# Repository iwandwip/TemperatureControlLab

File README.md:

# Temperature Control Lab - AP Monitor
The temperature control lab is an application of feedback control with an Arduino, an LED, two heaters, and two temperature sensors. The heater power output is adjusted to maintain a desired temperature setpoint. Thermal energy from the heater is transferred by conduction, convection, and radiation to the temperature sensor. Heat is also transferred away from the device to the surroundings.

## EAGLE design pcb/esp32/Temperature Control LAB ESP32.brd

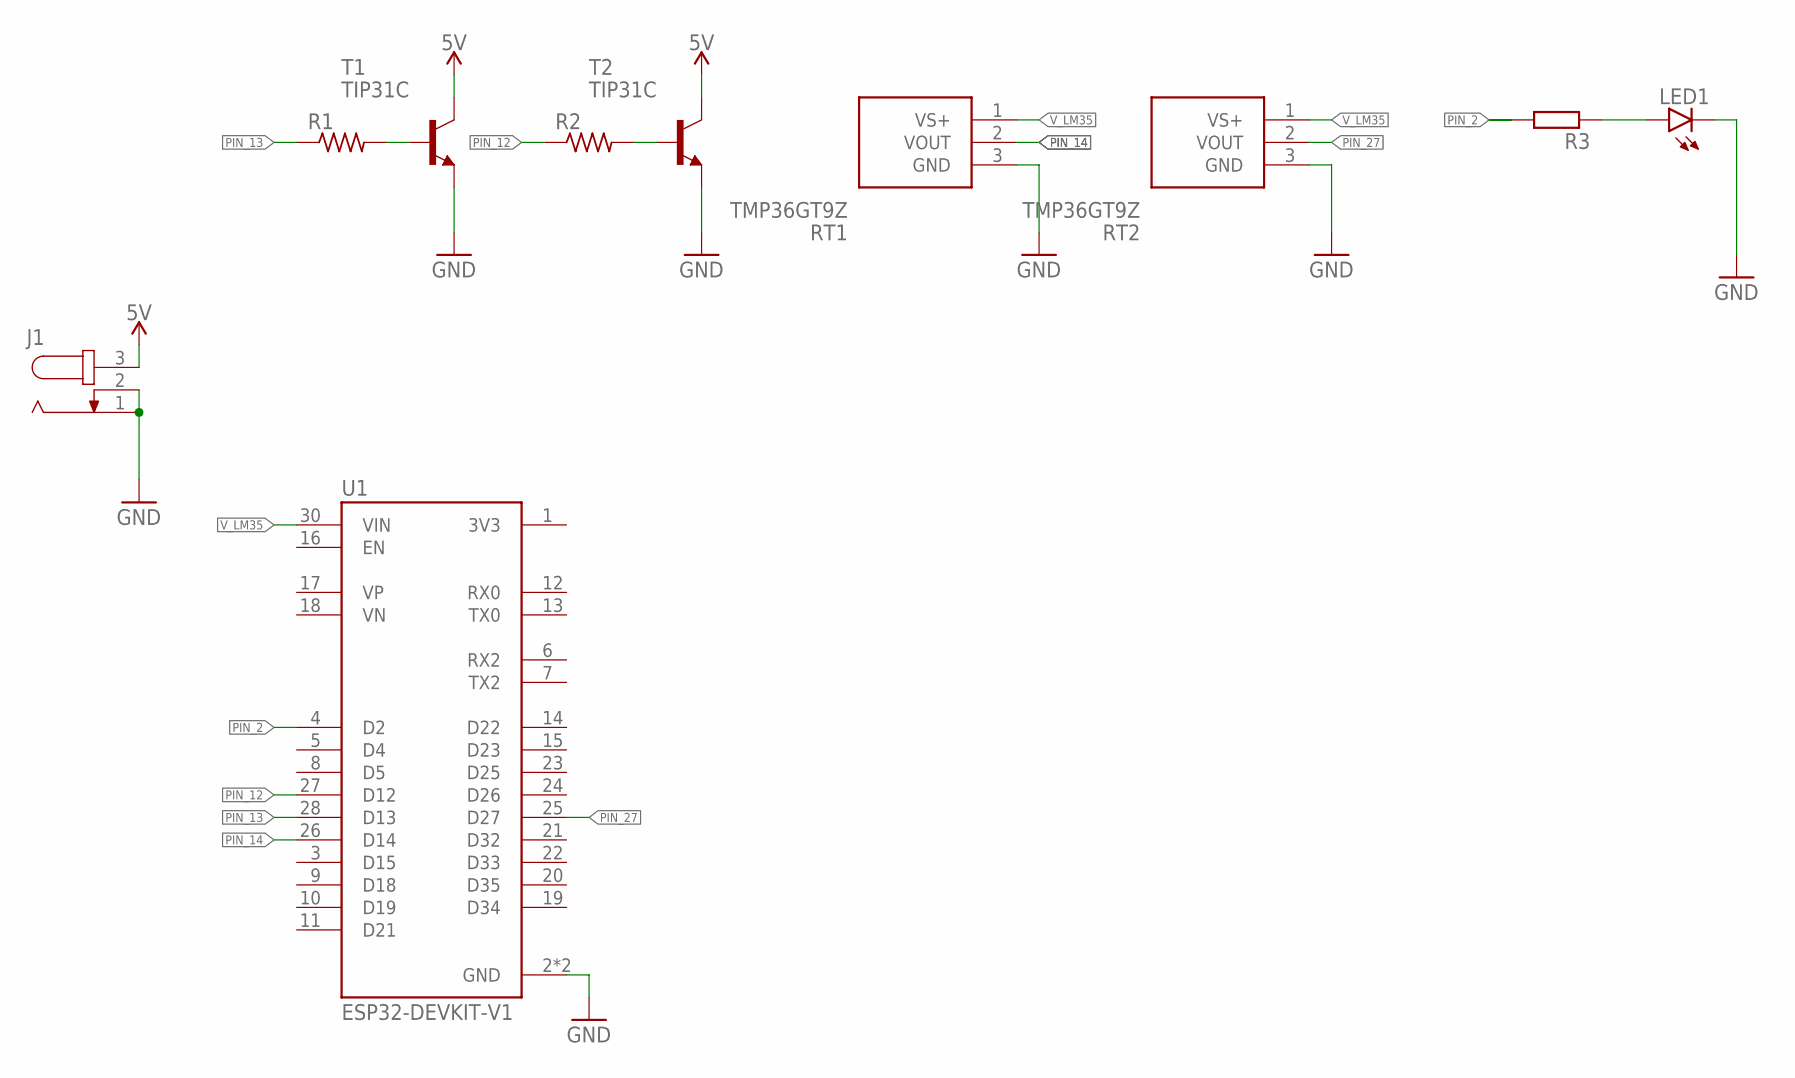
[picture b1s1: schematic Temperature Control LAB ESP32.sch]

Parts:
J1: JACK-PLUG0; SPC4077
LED1: LED5MM
R1, R2: R-US_M0805; M0805
R3: R-EU_R0805; R0805
RT1, RT2: TMP36GT9Z; TO-92
T1, T2: TIP31C; TO220
U1: ESP32-DEVKIT-V1; MODULE_ESP32_DEVKIT_V1

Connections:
5V: J1.3, T1.2 (C), T2.2 (C)
GND: J1.1, J1.2, LED1.K (C), RT1.3 (GND), RT2.3 (GND), T1.3 (E), T2.3 (E), U1.2 (GND), U1.29 (GND)
unnamed: R1.2, T1.1 (B)
unnamed: R2.2, T2.1 (B)
unnamed: LED1.A, R3.1
PIN_2: R3.2, U1.4 (D2)
PIN_12: R2.1, U1.27 (D12)
PIN_13: R1.1, U1.28 (D13)
PIN_14: RT1.2 (VOUT), U1.26 (D14)
PIN_27: RT2.2 (VOUT), U1.25 (D27)
V_LM35: RT1.1 (VS+), RT2.1 (VS+), U1.30 (VIN)

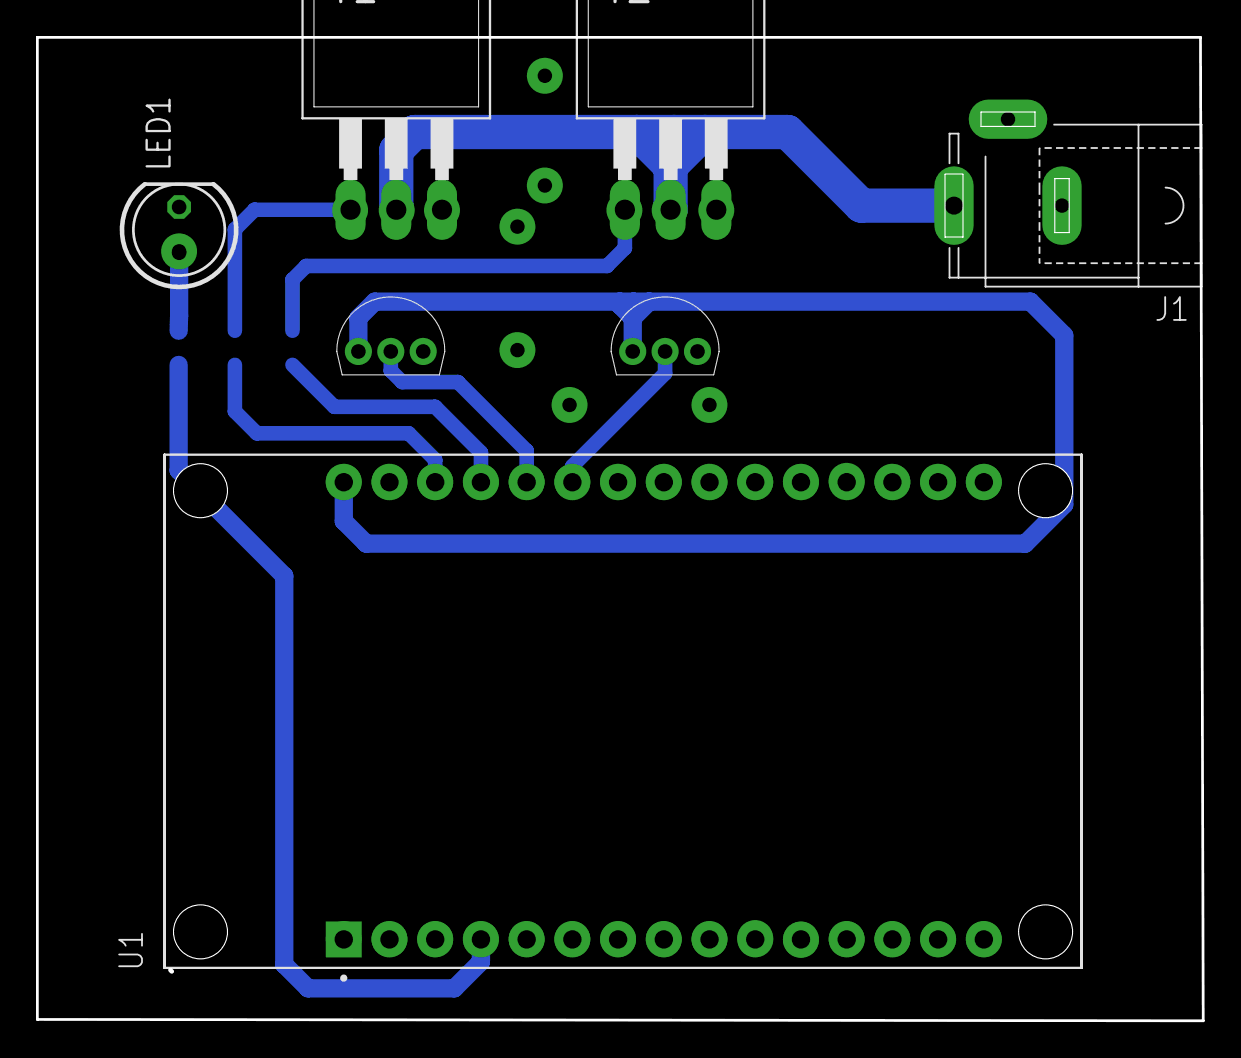
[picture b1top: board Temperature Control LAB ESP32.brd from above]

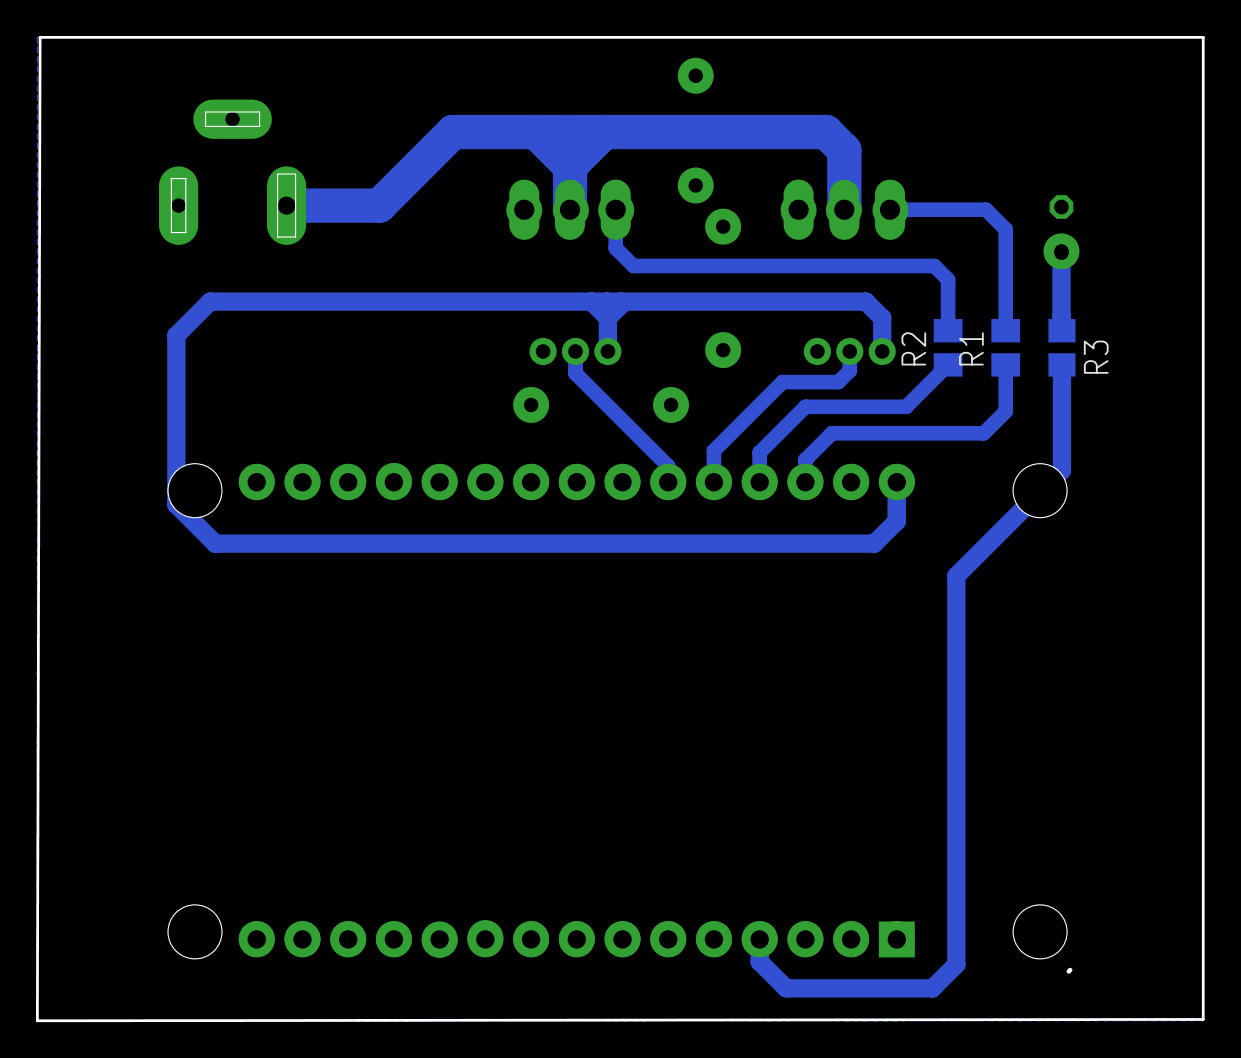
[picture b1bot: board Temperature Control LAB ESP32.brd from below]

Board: 2 copper layers, 64.7 x 54.5 mm, 10 parts (3 on the bottom side), 11 nets.

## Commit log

2024-01-18 test tc lab with 1khz freq

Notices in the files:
parts and their libraries:
SparkFun-PowerSymbols: Licensing: Creative Commons ShareAlike 4.0 International - https://creativecommons.org/licenses/by-sa/4.0
